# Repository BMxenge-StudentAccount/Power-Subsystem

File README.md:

# Power-Subsystem
 Power subsystem for a MicroMouse robot, developed by Bume Mxenge and Sinaye Toni as part of the EEE3088F Design Course.

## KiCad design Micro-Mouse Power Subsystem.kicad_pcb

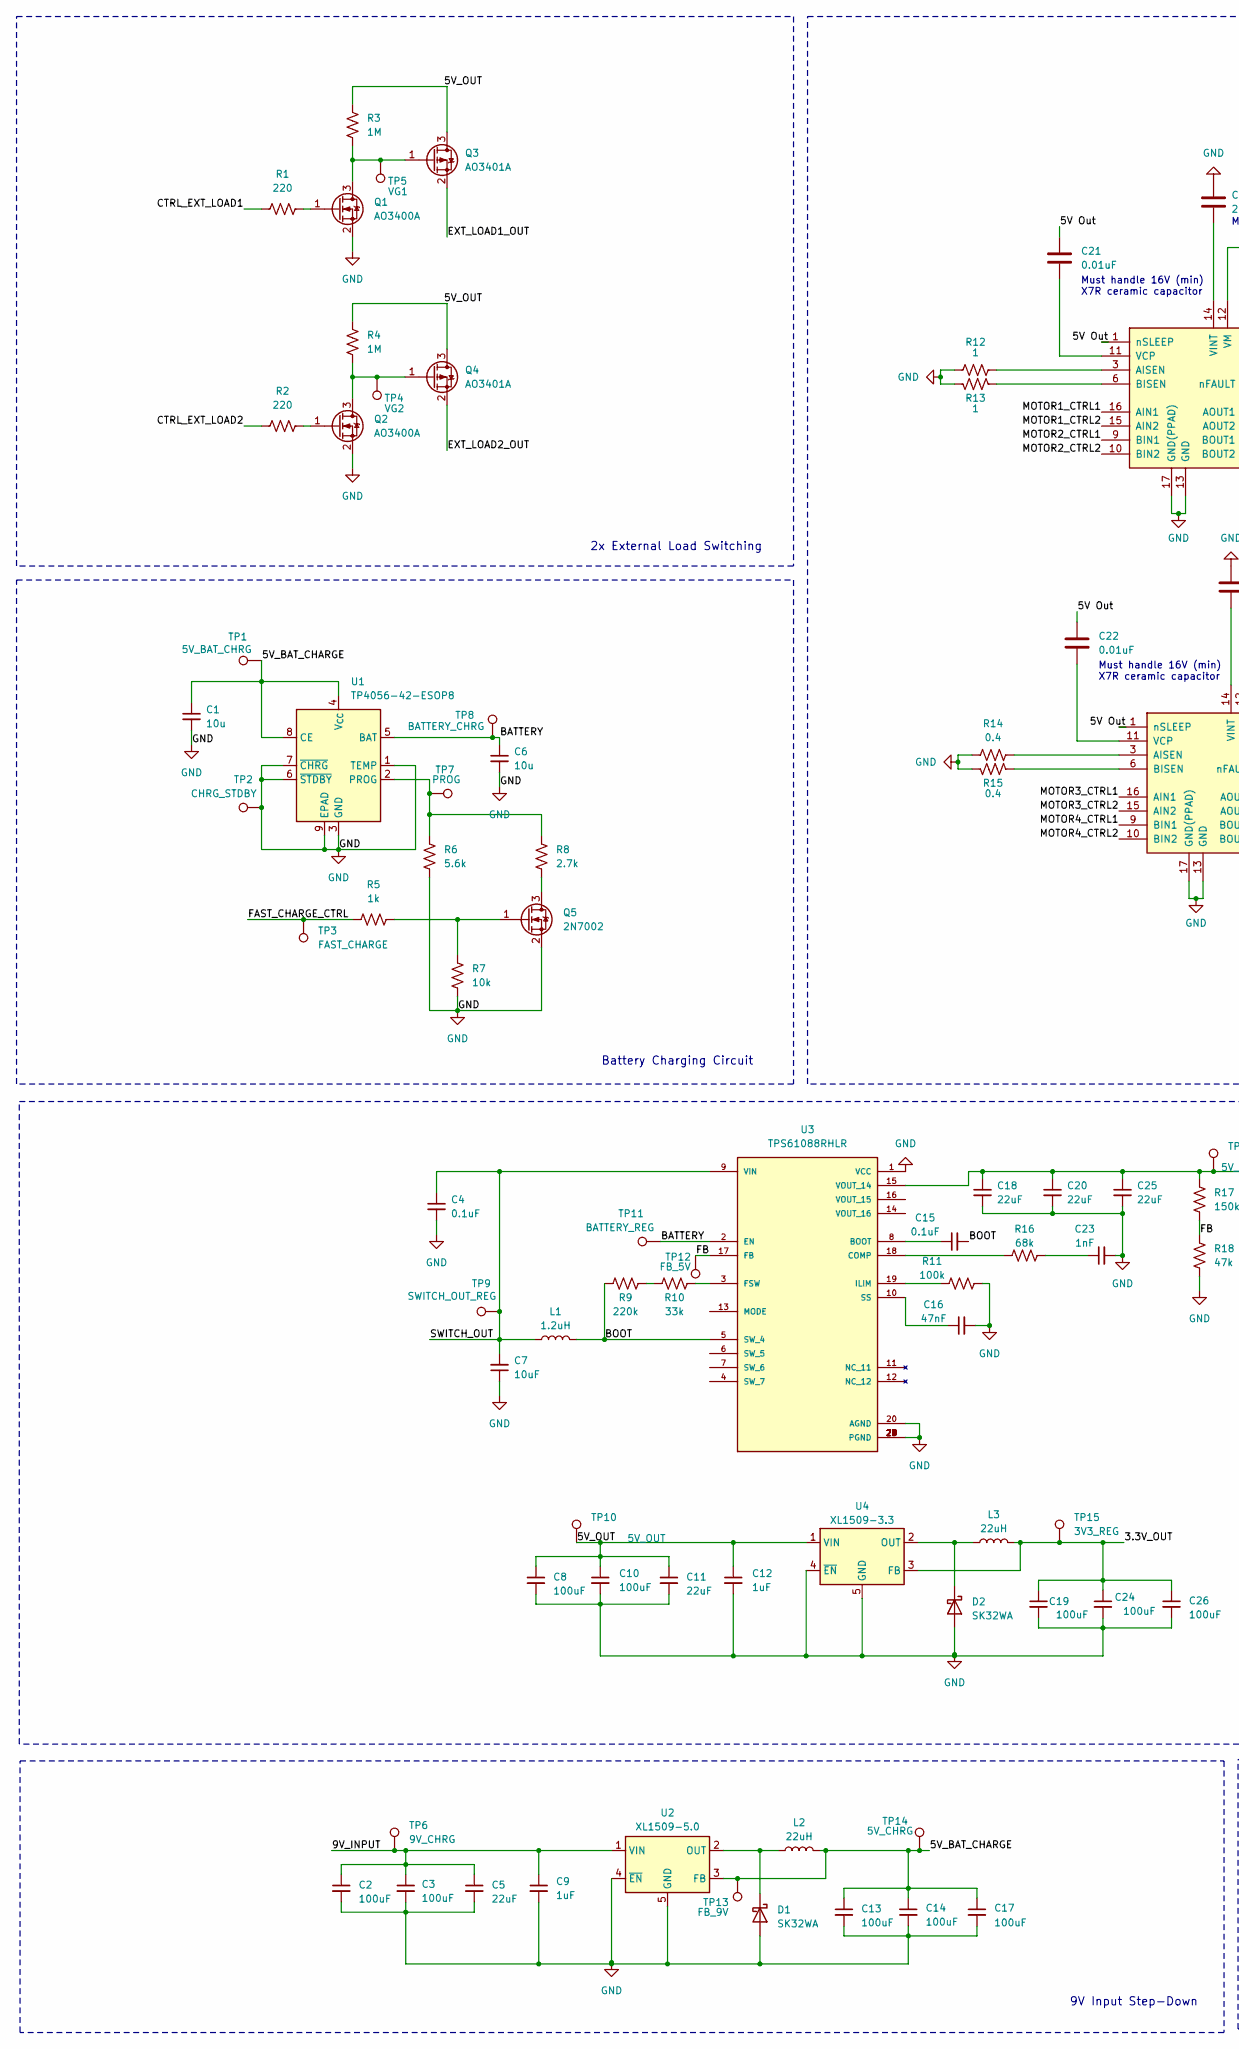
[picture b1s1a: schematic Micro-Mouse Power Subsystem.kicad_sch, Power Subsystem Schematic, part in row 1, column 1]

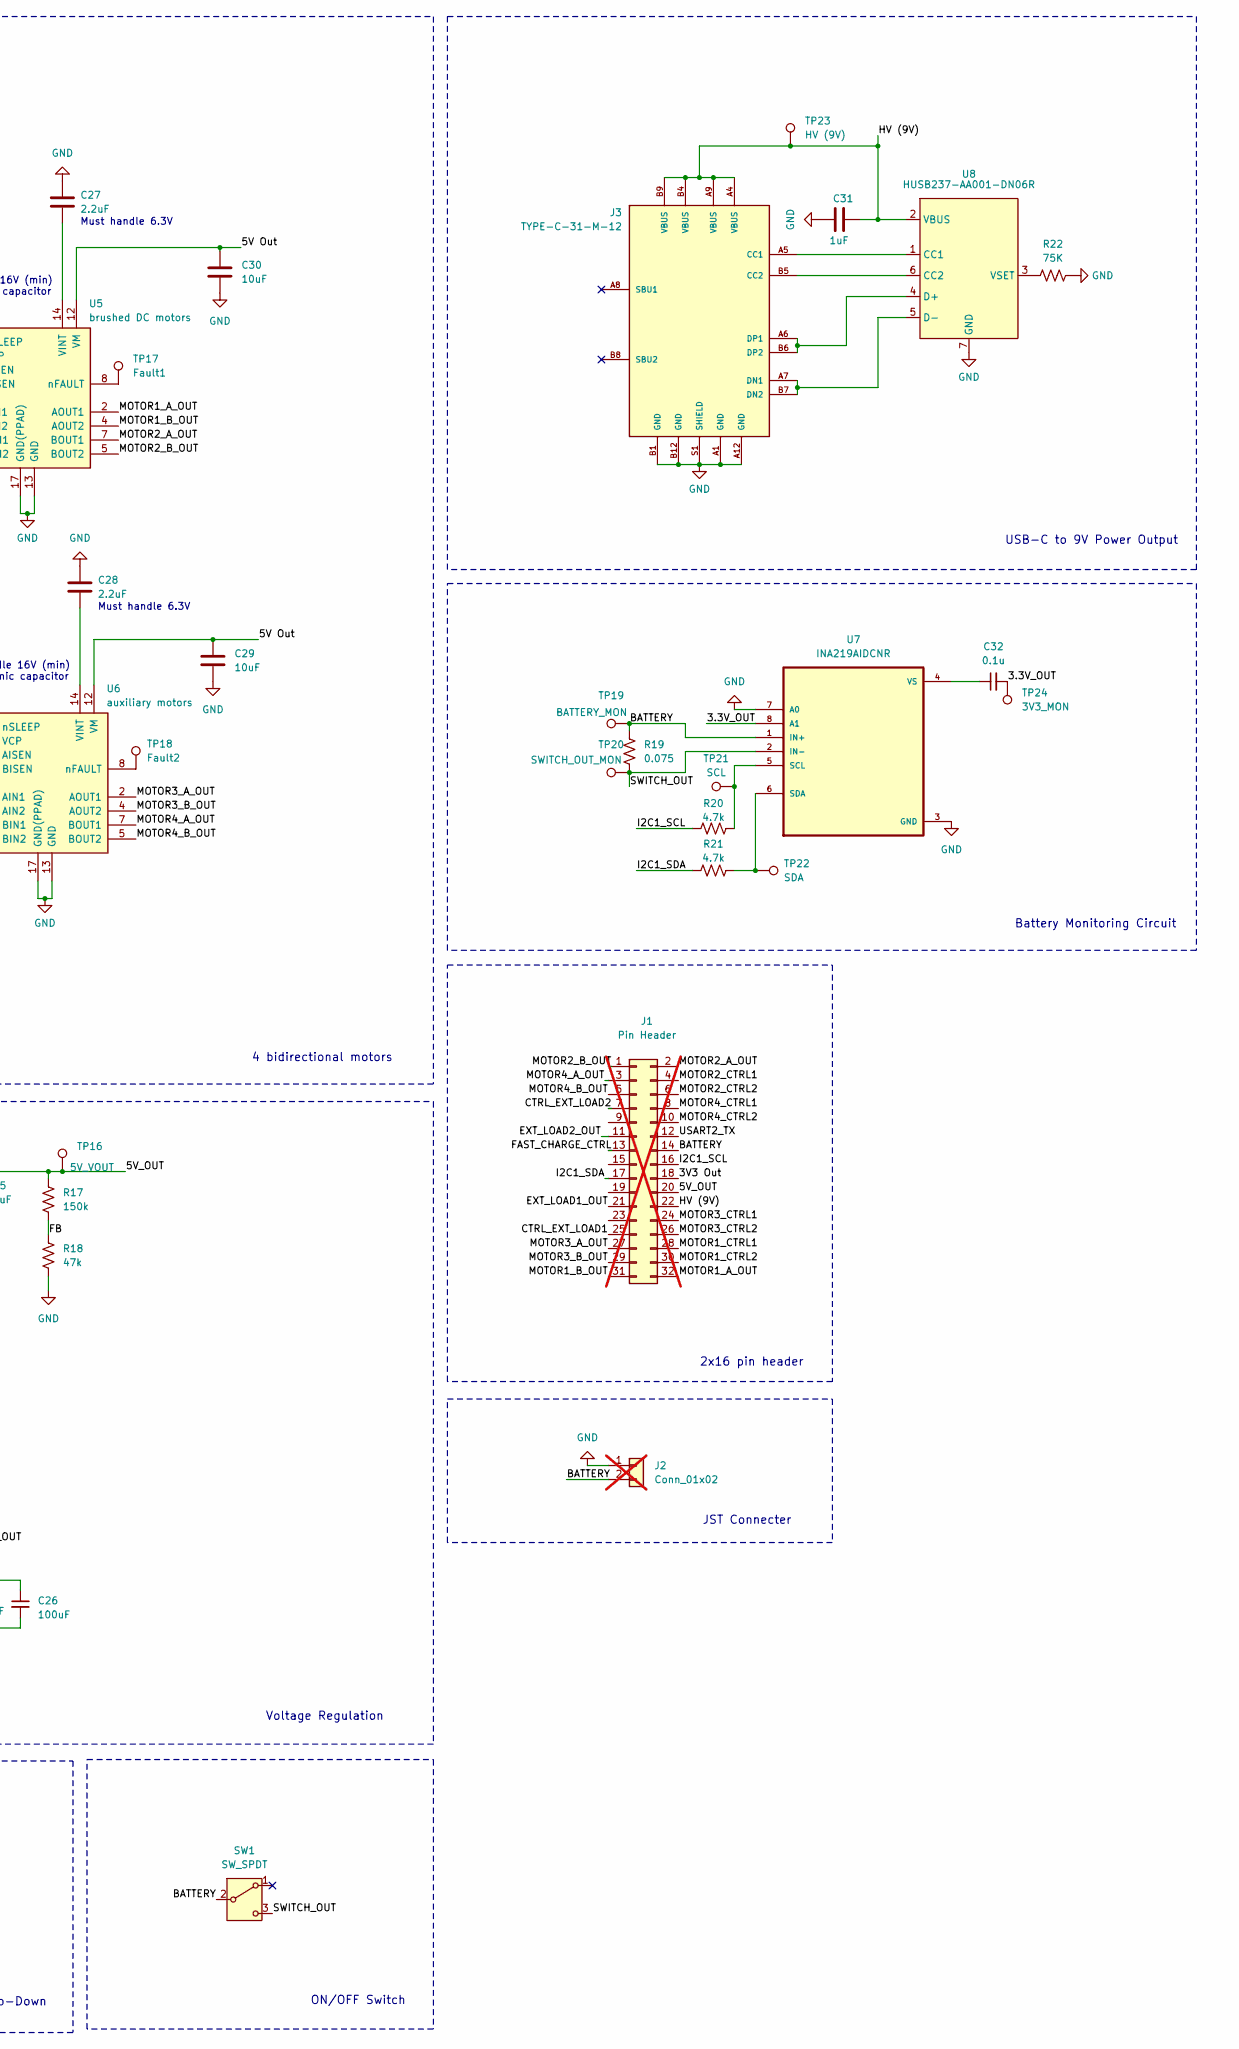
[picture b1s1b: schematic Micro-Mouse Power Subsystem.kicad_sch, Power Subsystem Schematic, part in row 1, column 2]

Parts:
C1, C6: 10u; C_0603_1608Metric
C2, C3, C8, C10, C17, C19, C24, C26: 100uF; C_1206_3216Metric
C4, C15: 0.1uF; C_0805_2012Metric
C5: 22uF; C_1206_3216Metric
C7: 10uF; C_0805_2012Metric
C9, C12: 1uF; C_0805_2012Metric
C11, C18, C20, C25: 22uF; C_0603_1608Metric
C13, C14: 100uF; C_1210_3225Metric
C16: 47nF; C_0805_2012Metric
C21, C22: 0.01uF; C_0603_1608Metric
C23: 1nF; C_0805_2012Metric
C27, C28: 2.2uF; C_0603_1608Metric
C29, C30: 10uF; C_0603_1608Metric
C31: 1uF; C_0603_1608Metric
C32: 0.1u; C_0805_2012Metric
D1, D2: SK32WA; D_SMA
J1: Pin Header; PinHeader_2x16_P2.54mm_Vertical; not fitted
J2: Conn_01x02; JST_PH_S2B-PH-K_1x02_P2.00mm_Horizontal; not fitted
J3: TYPE-C-31-M-12; USB_C_Receptacle_HRO_TYPE-C-31-M-12; PARTREV 2020.12.08
L1: 1.2uH; L_0805_2012Metric
L2, L3: 22uH; L_0603_1608Metric
Q1, Q2: AO3400A; SOT-23-3
Q3, Q4: AO3401A; SOT-23
Q5: 2N7002; SOT-23
R1, R2: 220; R_0805_2012Metric
R3, R4: 1M; R_0805_2012Metric
R5: 1k; R_0603_1608Metric
R6: 5.6k; R_0603_1608Metric
R7: 10k; R_0603_1608Metric
R8: 2.7k; R_0603_1608Metric
R9: 220k; R_0805_2012Metric
R10: 33k; R_0805_2012Metric
R11: 100k; R_0805_2012Metric
R12, R13: 1; R_0805_2012Metric_Pad1.20x1.40mm_HandSolder
R14, R15: 0.4; R_1206_3216Metric_Pad1.30x1.75mm_HandSolder
R16: 68k; R_0805_2012Metric
R17: 150k; R_0805_2012Metric
R18: 47k; R_0805_2012Metric
R19: 0.075; R_0805_2012Metric
R20, R21: 4.7k; R_0805_2012Metric
R22: 75K; R_0603_1608Metric
SW1: SW_SPDT; SolderWire-0.75sqmm_1x03_P4.8mm_D1.25mm_OD2.3mm
TP1: 5V_BAT_CHRG; TestPoint_Pad_1.5x1.5mm
TP2: CHRG_STDBY; TestPoint_Pad_1.5x1.5mm
TP3: FAST_CHARGE; TestPoint_Pad_1.5x1.5mm
TP4: VG2; TestPoint_Pad_1.5x1.5mm
TP5: VG1; TestPoint_Pad_1.5x1.5mm
TP6: 9V_CHRG; TestPoint_Pad_1.5x1.5mm
TP7: PROG; TestPoint_Pad_1.5x1.5mm
TP8: BATTERY_CHRG; TestPoint_Pad_1.5x1.5mm
TP9: SWITCH_OUT_REG; TestPoint_Pad_1.5x1.5mm
TP10: 5V_OUT; TestPoint_Pad_1.5x1.5mm
TP11: BATTERY_REG; TestPoint_Pad_1.5x1.5mm
TP12: FB_5V; TestPoint_Pad_1.5x1.5mm
TP13: FB_9V; TestPoint_Pad_1.5x1.5mm
TP14: 5V_CHRG; TestPoint_Pad_1.5x1.5mm
TP15: 3V3_REG; TestPoint_Pad_1.5x1.5mm
TP16: 5V_VOUT; TestPoint_Pad_1.5x1.5mm
TP17: Fault1; TestPoint_Pad_1.5x1.5mm
TP18: Fault2; TestPoint_Pad_1.5x1.5mm
TP19: BATTERY_MON; TestPoint_Pad_1.5x1.5mm
TP20: SWITCH_OUT_MON; TestPoint_Pad_1.5x1.5mm
TP21: SCL; TestPoint_Pad_1.5x1.5mm
TP22: SDA; TestPoint_Pad_1.5x1.5mm
TP23: HV (9V); TestPoint_Pad_1.5x1.5mm
TP24: 3V3_MON; TestPoint_Pad_1.5x1.5mm
U1: TP4056-42-ESOP8; SOIC-8-1EP_3.9x4.9mm_P1.27mm_EP2.41x3.3mm_ThermalVias
U2: XL1509-5.0; SOIC-8_3.9x4.9mm_P1.27mm
U3: TPS61088RHLR; IC_TPS61088RHLR; PARTREV 4219071/A 05/2017
U4: XL1509-3.3; SOIC-8_3.9x4.9mm_P1.27mm
U5: brushed DC motors; HTSSOP-16-1EP_4.4x5mm_P0.65mm_EP3.4x5mm_Mask2.46x2.31mm_The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
U6: auxiliary motors; HTSSOP-16-1EP_4.4x5mm_P0.65mm_EP3.4x5mm_Mask2.46x2.31mm_The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
U7: INA219AIDCNR; SOT-23-8
U8: HUSB237-AA001-DN06R; DFN-6-1EP_2x2mm_P0.65mm_EP1x1.6mm

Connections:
/3.3V_OUT: C19.1, C24.1, C26.1, C32.2, L3.2, TP15.1, TP24.1, U4.3 (FB), U7.8 (A1)
/3V3 Out: J1.18
/5V Out: C21.1, C22.1, C29.1, C30.1, U5.1 (nSLEEP), U5.12 (VM), U6.1 (nSLEEP), U6.12 (VM)
/5V_BAT_CHARGE: C1.1, C13.1, C14.1, C17.1, L2.2, TP1.1, TP13.1, TP14.1, U1.4 (V_{CC}), U1.8 (CE), U2.3 (FB)
/5V_OUT: C8.1, C10.1, C11.1, C12.1, C18.1, C20.1, C25.1, J1.20, Q3.3 (D), Q4.3 (D), R3.1, R4.1, R17.2, TP10.1, TP16.1, U3.15 (VOUT_14), U4.1 (VIN)
/9V_INPUT: C2.1, C3.1, C5.1, C9.1, TP6.1, U2.1 (VIN)
/BATTERY: C6.1, J1.14, J2.2, R19.2, SW1.2 (B), TP8.1, TP11.1, TP19.1, U1.5 (BAT), U3.2 (EN), U7.1 (IN+)
/BOOT: C15.2, L1.2, R9.1, U3.5 (SW_4)
/CTRL_EXT_LOAD1: J1.25, R1.1
/CTRL_EXT_LOAD2: J1.7, R2.1
/EXT_LOAD1_OUT: J1.21, Q3.2 (S)
/EXT_LOAD2_OUT: J1.11, Q4.2 (S)
/FAST_CHARGE_CTRL: R5.1, TP3.1
/FAST_CHARGE_CTRL: J1.13
/FB: R17.1, R18.2, TP12.1, U3.17 (FB)
/HV (9V): C31.1, J1.22, J3.A4 (VBUS), J3.A9 (VBUS), J3.B4 (VBUS), J3.B9 (VBUS), TP23.1, U8.2 (VBUS)
/I2C1_SCL: R20.2
/I2C1_SCL: J1.16
/I2C1_SDA: R21.1
/I2C1_SDA: J1.17
/MOTOR1_A_OUT: U5.2 (AOUT1)
/MOTOR1_A_OUT: J1.32
/MOTOR1_B_OUT: J1.31, U5.4 (AOUT2)
/MOTOR1_CTRL1: J1.28, U5.16 (AIN1)
/MOTOR1_CTRL2: J1.30, U5.15 (AIN2)
/MOTOR2_A_OUT: J1.2, U5.7 (BOUT1)
/MOTOR2_B_OUT: J1.1, U5.5 (BOUT2)
/MOTOR2_CTRL1: J1.4, U5.9 (BIN1)
/MOTOR2_CTRL2: J1.6, U5.10 (BIN2)
/MOTOR3_A_OUT: J1.27, U6.2 (AOUT1)
/MOTOR3_B_OUT: J1.29, U6.4 (AOUT2)
/MOTOR3_CTRL1: J1.24, U6.16 (AIN1)
/MOTOR3_CTRL2: J1.26, U6.15 (AIN2)
/MOTOR4_A_OUT: J1.3, U6.7 (BOUT1)
/MOTOR4_B_OUT: J1.5, U6.5 (BOUT2)
/MOTOR4_CTRL1: J1.8, U6.9 (BIN1)
/MOTOR4_CTRL2: J1.10, U6.10 (BIN2)
/SWITCH_OUT: C4.1, C7.2, L1.1, R19.1, SW1.3 (C), TP9.1, TP20.1, U3.9 (VIN), U7.2 (IN-)
/USART2_TX: J1.12
GND: C1.2, C2.2, C3.2, C4.2, C5.2, C6.2, C7.1, C8.2, C9.2, C10.2, C11.2, C12.2, C13.2, C14.2, C16.2, C17.2, C18.2, C19.2, C20.2, C23.2, C24.2, C25.2, C26.2, C27.1, C28.1, C29.2, C30.2, C31.2, D1.2 (A), D2.2 (A), J2.1, J3.A1 (GND), J3.A12 (GND), J3.B1 (GND), J3.B12 (GND), J3.S1 (SHIELD), Q1.2 (S), Q2.2 (S), Q5.2 (S), R6.2, R7.2, R11.2, R12.1, R13.1, R14.1, R15.1, R18.1, R22.2, TP2.1, U1.1 (TEMP), U1.3 (GND), U1.6 (~STDBY), U1.7 (~CHRG), U1.9 (EPAD), U2.4 (~EN), U2.5 (GND), U2.6 (GND), U2.7 (GND), U2.8 (GND), U3.1 (VCC), U3.20 (AGND), U3.21 (PGND), U3.22 (PGND), U3.23 (PGND), U3.24 (PGND), U3.25 (PGND), U3.26 (PGND), U3.27 (PGND), U3.28 (PGND), U3.29 (PGND), U4.4 (~EN), U4.5 (GND), U4.6 (GND), U4.7 (GND), U4.8 (GND), U5.13 (GND), U5.17 (GND(PPAD)), U6.13 (GND), U6.17 (GND(PPAD)), U7.3 (GND), U7.7 (A0), U8.7 (GND)
unnamed: C23.1, R16.2
unnamed: D1.1 (K), L2.1, U2.2 (OUT)
unnamed: D2.1 (K), L3.1, U4.2 (OUT)
unnamed: J3.A5 (CC1), U8.1 (CC1)
unnamed: J3.B5 (CC2), U8.6 (CC2)
unnamed: J3.A7 (DN1), J3.B7 (DN2), U8.5 (D-)
unnamed: J3.A6 (DP1), J3.B6 (DP2), U8.4 (D+)
unnamed: Q1.3 (D), Q3.1 (G), R3.2, TP5.1
unnamed: Q1.1 (G), R1.2
unnamed: Q2.3 (D), Q4.1 (G), R4.2, TP4.1
unnamed: Q2.1 (G), R2.2
unnamed: Q5.3 (D), R8.2
unnamed: Q5.1 (G), R5.2, R7.1
unnamed: R9.2, R10.1
unnamed: R6.1, R8.1, TP7.1, U1.2 (PROG)
unnamed: C15.1, U3.8 (BOOT)
unnamed: R16.1, U3.18 (COMP)
unnamed: R10.2, U3.3 (FSW)
unnamed: R11.1, U3.19 (ILIM)
unnamed: C16.1, U3.10 (SS)
unnamed: R12.2, U5.3 (AISEN)
unnamed: R13.2, U5.6 (BISEN)
unnamed: C21.2, U5.11 (VCP)
unnamed: C27.2, U5.14 (VINT)
unnamed: TP17.1, U5.8 (nFAULT)
unnamed: R14.2, U6.3 (AISEN)
unnamed: R15.2, U6.6 (BISEN)
unnamed: C22.2, U6.11 (VCP)
unnamed: C28.2, U6.14 (VINT)
unnamed: TP18.1, U6.8 (nFAULT)
unnamed: R20.1, TP21.1, U7.5 (SCL)
unnamed: R21.2, TP22.1, U7.6 (SDA)
unnamed: C32.1, U7.4 (VS)
unnamed: R22.1, U8.3 (VSET)

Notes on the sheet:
USB-C to 9V Power Output
Must handle 6.3V
2x External Load Switching
9V Input Step-Down
Must handle 16V (min) X7R ceramic capacitor
4 bidirectional motors
JST Connecter
Battery Charging Circuit
ON/OFF Switch
Battery Monitoring Circuit
2x16 pin header
Voltage Regulation

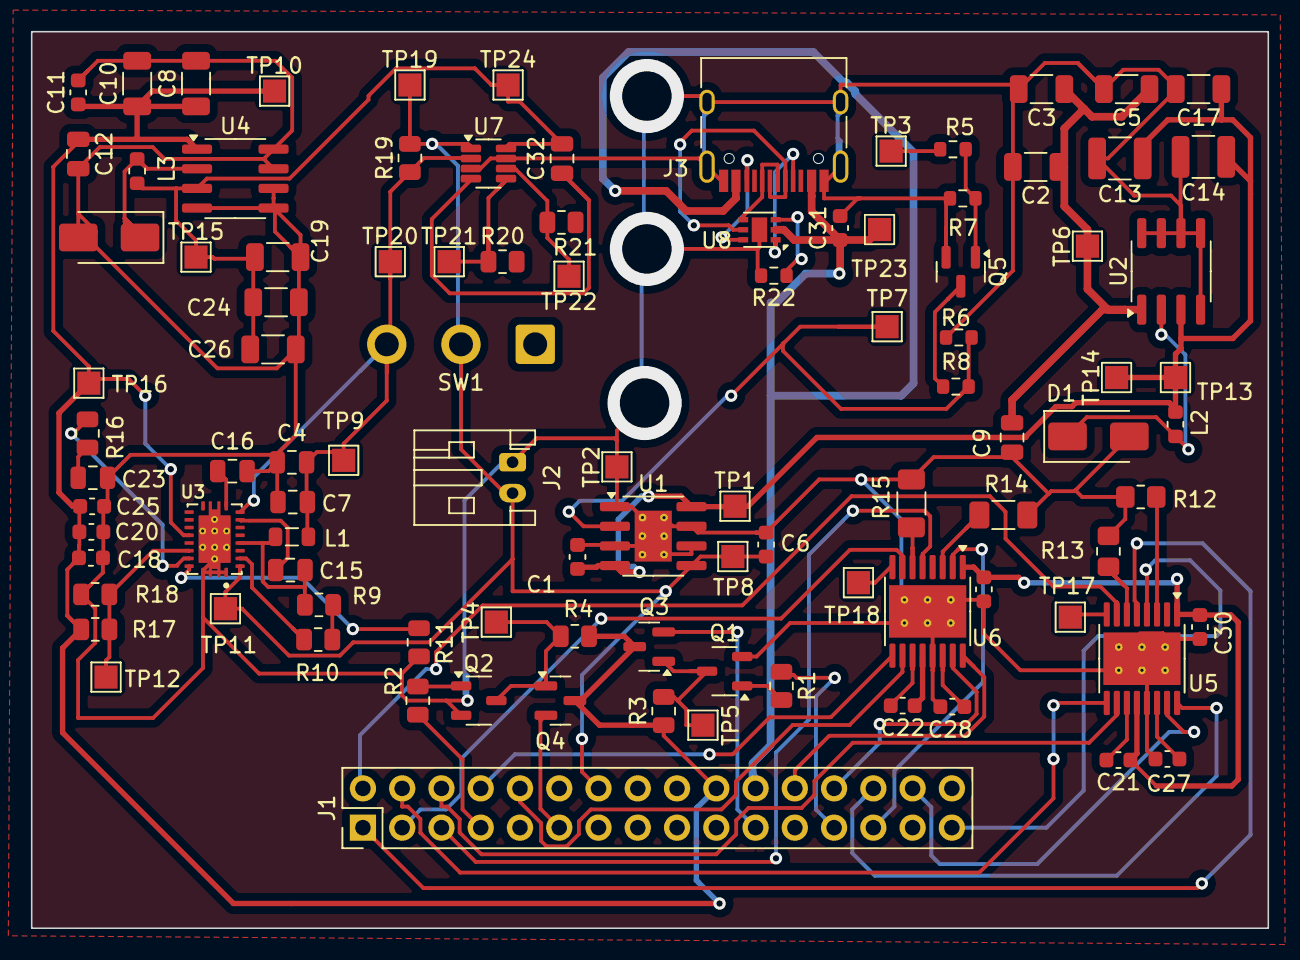
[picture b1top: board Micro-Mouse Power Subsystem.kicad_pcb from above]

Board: 2 copper layers, 80.0 x 58.0 mm, 100 parts (0 on the bottom side), 65 nets.

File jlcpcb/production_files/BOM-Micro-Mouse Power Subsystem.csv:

Comment,Designator,Footprint,LCSC,Quantity
22uF,"C11,C5",C_0603_1608Metric,C12891,2
2.7k,R8,R_0603_1608Metric,C13167,1
100k,R11,R_0805_2012Metric,C149504,1
100uF,"C10,C17,C19,C2,C24,C26,C3,C8",C_1206_3216Metric,C15008,8
AO3401A,"Q3,Q4",SOT-23,C15127,2
0.075,R19,R_0805_2012Metric,C158146,1
1uF,C31,C_0603_1608Metric,C15849,1
10uF,C7,C_0805_2012Metric,C15850,1
TP4056-42-ESOP8,U1,SOIC-8-1EP_3.9x4.9mm_P1.27mm_EP2.41x3.3mm_ThermalVias,C16581,1
TYPE-C-31-M-12,J3,USB_C_Receptacle_HRO_TYPE-C-31-M-12,C165948,1
150k,R17,R_0805_2012Metric,C17470,1
1M,"R3,R4",R_0805_2012Metric,C17514,2
220k,R9,R_0805_2012Metric,C17556,1
220,"R1,R2",R_0805_2012Metric,C17557,2
33k,R10,R_0805_2012Metric,C17633,1
4.7k,"R20,R21",R_0805_2012Metric,C17673,2
47k,R18,R_0805_2012Metric,C17713,1
68k,R16,R_0805_2012Metric,C17801,1
SW_SPDT,SW1,SolderWire-0.75sqmm_1x03_P4.8mm_D1.25mm_OD2.3mm,C19189121,1
10u,"C1,C29,C30,C6",C_0603_1608Metric,C19702,4
AO3400A,"Q1,Q2",SOT-23-3,C20917,2
1k,R5,R_0603_1608Metric,C21190,1
HUSB237-AA001-DN06R,U8,DFN-6-1EP_2x2mm_P0.65mm_EP1x1.6mm,C22373734,1
SK32WA,"D1,D2",D_SMA,C22452,2
5.6k,R6,R_0603_1608Metric,C23189,1
75K,R22,R_0603_1608Metric,C23242,1
2.2uF,"C27,C28",C_0603_1608Metric,C23630,2
0.4,"R14,R15",R_1206_3216Metric_Pad1.30x1.75mm_HandSolder,C247521,2
1,"R12,R13",R_0805_2012Metric_Pad1.20x1.40mm_HandSolder,C25271,2
10k,R7,R_0603_1608Metric,C25804,1
XL1509-3.3,U4,SOIC-8_3.9x4.9mm_P1.27mm,C2681226,1
0.1uF,"C15,C32,C4",C_0805_2012Metric,C28233,3
1uF,"C12,C9",C_0805_2012Metric,C28323,2
22uH,"L2,L3",L_0603_1608Metric,C361669,2
1nF,C23,C_0805_2012Metric,C46653,1
brushed DC motors,"U5,U6",HTSSOP-16-1EP_4.4x5mm_P0.65mm_EP3.4x5mm_Mask2.46x2.31mm_ThermalVias,C50506,2
47nF,C16,C_0805_2012Metric,C53134,1
1.2uH,L1,L_0805_2012Metric,C5563768,1
0.01uF,"C21,C22",C_0603_1608Metric,C57112,2
22uF,"C18,C20,C25",C_0603_1608Metric,C59461,3
XL1509-5.0,U2,SOIC-8_3.9x4.9mm_P1.27mm,C61063,1
2N7002,Q5,SOT-23,C8545,1
100uF,"C13,C14",C_1210_3225Metric,C8649,2
TPS61088RHLR,U3,IC_TPS61088RHLR,C87357,1
INA219AIDCNR,U7,SOT-23-8,C87469,1

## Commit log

2025-03-25 Added Initial Project File
2025-03-25 Re-added project files.
    First try didn't work
2025-03-25 This was just a check to see that everything is working
2025-03-26 Added the Battery Charging Circuit and footprints
2025-03-26 Removed old backup
2025-03-26 Updated PCB layout to include battery charging circuit
2025-03-26 start of motor
2025-03-27 V1
    - 2x ext load switching is now implemented using mosfets
    - 4 bidirectional motors done
    - Assigned JLCP components
    - Just moved components into groups in PCB mode to make it easier for when we have to add wires
2025-03-27 Added the step down for 9V to 5V (for charging IC) and part of the voltage regulation (5V to 3.3V), no footprints yet
2025-03-27 Add KiCad symbols and footprints library as submodule
2025-03-27 yeah neh, hold up
2025-03-27 Sorry, I forgot to change to my branch
2025-03-27 Added a library for custom components
2025-03-28 V1.1
    - Refined Motor drivers
    - Added USBC
    - Added JST (don't know connections yet)
2025-03-28 It's just the back up file
2025-03-28 Sinaye's Changes
2025-03-28 I don't know what's happening
2025-03-28 still v1.1
    -added switch
2025-03-28 switch added
2025-03-28 V2
    - all schematics are uploaded
    - missing a few footprints from Sinaye
2025-03-28 Added footprints and adjusted labelling
2025-03-28 Sinaye
2025-03-28 Added the zip into additional componenets of the missing footprint, Maybe you'll have better luck
2025-03-28 V2.1
2025-03-28 IDK mahn
2025-03-28 save
2025-03-28 replaced pcb
2025-04-08 First submision
2025-04-08 Added all my test points (as well as missing input for my charging circuit -- wild that i missed it
2025-04-09 pcb sections
2025-04-09 My laptop is dying
2025-04-09 Bume's components placed in outline
2025-04-09 Done with the pcb layout -- hopefully
2025-04-23 updated pcb layout
